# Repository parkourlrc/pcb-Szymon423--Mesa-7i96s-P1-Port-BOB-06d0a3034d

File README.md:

# Mesa 7i96S P1 I/O Breakout Board

This is a breakout board for the **P1 (DB25) expansion port of the [Mesa 7i96S](https://mesanet.com/)**. It turns the 17 raw 3.3 V GPIO pins of P1 into
**12 galvanically isolated 24 V inputs** and **5 solid-state relay outputs**. The outputs are on pluggable screw terminals, and the board sits on a 3D-printed DIN-rail mount.

| Front | Back |
| :---: | :--: |
|  |  |

---

## Features

- **12 inputs, 24 V, optically isolated.** Each input has a TLP293 optocoupler, a 74HC14 Schmitt-trigger buffer, a bidirectional TVS (SMF30CA), a ferrite-bead filter and a status LED.
- **5 outputs, solid-state relays.** The CPC1017N SSRs give isolated, polarity-free contacts that switch AC or DC. Each output has a status LED.
- **Pluggable 3.5 mm terminal blocks** (Phoenix MCV-style) on the field side.
- **26-pin IDC header** that connects to the 7i96S P1 with a standard IDC26 ⇄ DB25 ribbon cable.
- **Powered from the Mesa card.** The logic side takes +5 V from P1, behind a 100 mA fuse. The board needs no extra logic supply.
- **3D-printed DIN-rail mount.** STL, 3MF and Blender source are included.

## Specifications

| Parameter | Value |
| --- | --- |
| Inputs | 12, isolated, sourcing (PNP / +24 V = active) |
| Input voltage | 24 V nominal, clamped by 30 V TVS |
| Input current | ≈ 4–5 mA @ 24 V |
| Input isolation | Optocoupler; the input common (`GND` terminals) is separate from Mesa GND |
| Outputs | 5, SSR contacts (CPC1017N), AC/DC |
| Output voltage | max **30 V** |
| Output current | max **100 mA** per channel |
| Logic supply | +5 V from Mesa P1, fused 100 mA |
| PCB size | 52.5 × 98 mm, 2 layers |

## Pinout

### Field terminals (top → bottom, as printed on the silkscreen)

| Terminal | Signal | Mesa pin | LinuxCNC HAL pin |
| --- | --- | --- | --- |
| J5.1 | In12 | IO40 | `hm2_7i96s.0.gpio.040.in` |
| J5.2 | In11 | IO41 | `hm2_7i96s.0.gpio.041.in` |
| J5.3 | In10 | IO42 | `hm2_7i96s.0.gpio.042.in` |
| J5.4 | In9  | IO43 | `hm2_7i96s.0.gpio.043.in` |
| J5.5 | In8  | IO44 | `hm2_7i96s.0.gpio.044.in` |
| J5.6 | In7  | IO45 | `hm2_7i96s.0.gpio.045.in` |
| J3.1 | In6  | IO34 | `hm2_7i96s.0.gpio.034.in` |
| J3.2 | In5  | IO35 | `hm2_7i96s.0.gpio.035.in` |
| J3.3 | In4  | IO36 | `hm2_7i96s.0.gpio.036.in` |
| J3.4 | In3  | IO37 | `hm2_7i96s.0.gpio.037.in` |
| J3.5 | In2  | IO38 | `hm2_7i96s.0.gpio.038.in` |
| J3.6 | In1  | IO39 | `hm2_7i96s.0.gpio.039.in` |
| J4.1, J4.2 | GND (input common, isolated) | – | – |
| J4.3 / J4.4 | Out5 A / B | IO46 | `hm2_7i96s.0.gpio.046.out` |
| J4.5 / J4.6 | Out4 A / B | IO47 | `hm2_7i96s.0.gpio.047.out` |
| J6.1 / J6.2 | Out3 A / B | IO48 | `hm2_7i96s.0.gpio.048.out` |
| J6.3 / J6.4 | Out2 A / B | IO49 | `hm2_7i96s.0.gpio.049.out` |
| J6.5 / J6.6 | Out1 A / B | IO50 | `hm2_7i96s.0.gpio.050.out` |

### Mesa connector (J7, IDC 2×13)

| J7 pin | DB25 pin* | Signal |
| --- | --- | --- |
| 1, 2, 3, 4, 5, 6, 7, 8, 9 | 1, 14, 2, 15, 3, 16, 4, 17, 5 | IO34 … IO42 |
| 11, 13, 15 | 6, 7, 8 | IO43, IO44, IO45 |
| 17, 19, 21, 23, 25 | 9, 10, 11, 12, 13 | IO46 … IO50 |
| 10, 12, 14, 16 | 18, 19, 20, 21 | GND |
| 18, 20, 22, 24 | 22, 23, 24, 25 | +5 V (from Mesa) |
| 26 | – | not connected |

\* With a standard flat IDC26 ⇄ DB25 cable.

> [!IMPORTANT]
> The board takes its logic power from the +5 V on the P1 connector. Check in the 7i96S manual that +5 V is enabled on P1.

## Wiring

**Inputs.** Each input is active when +24 V is applied to the `InX` terminal relative to the `GND` terminals (J4.1/J4.2). Connect the 0 V of your 24 V field supply to `GND`. This suits PNP (sourcing) sensors, switches to +24 V, and similar. The input common is **not** connected to Mesa ground, so isolation is preserved.

```
+24V ──[switch / PNP sensor]──► InX
0V   ─────────────────────────► GND (J4.1 / J4.2)
```

**Outputs.** Each output is a floating SSR contact between `OutXA` and `OutXB`. Wire it like a relay contact in series with the load. It works for DC or AC up to 30 V and 100 mA, which is enough for a relay coil, a pilot light or a PLC input. Use an external relay or contactor for bigger loads, and use a flyback diode on inductive DC loads.

```
+V ──[load]──► OutXA   OutXB ──► 0V
```

## LinuxCNC configuration

The P1 pins must be configured as plain GPIO in the 7i96S firmware. Input polarity is not inverted: an active input reads `TRUE`. An output set to `TRUE` closes the SSR.

```hal
# Outputs: P1 GPIO are inputs by default
setp hm2_7i96s.0.gpio.046.is_output true
setp hm2_7i96s.0.gpio.047.is_output true
setp hm2_7i96s.0.gpio.048.is_output true
setp hm2_7i96s.0.gpio.049.is_output true
setp hm2_7i96s.0.gpio.050.is_output true

# Examples
net spindle-cw     spindle.0.forward          => hm2_7i96s.0.gpio.050.out   # Out1
net coolant-flood  iocontrol.0.coolant-flood  => hm2_7i96s.0.gpio.049.out   # Out2

net probe-in       hm2_7i96s.0.gpio.039.in    => motion.probe-input         # In1
net tool-setter    hm2_7i96s.0.gpio.038.in    => motion.digital-in-00       # In2
```

## License

This project is licensed under [**Creative Commons Attribution 4.0 International (CC BY 4.0)**](LICENSE).

You may use, modify, manufacture and sell the design, including commercially, provided that you **credit the author**. For example:

> Based on *Mesa 7i96S P1 I/O Breakout Board* by Szymon Wąchała – https://github.com/Szymon423/24-DB25-BOB-IO

Author: **Szymon Wąchała**

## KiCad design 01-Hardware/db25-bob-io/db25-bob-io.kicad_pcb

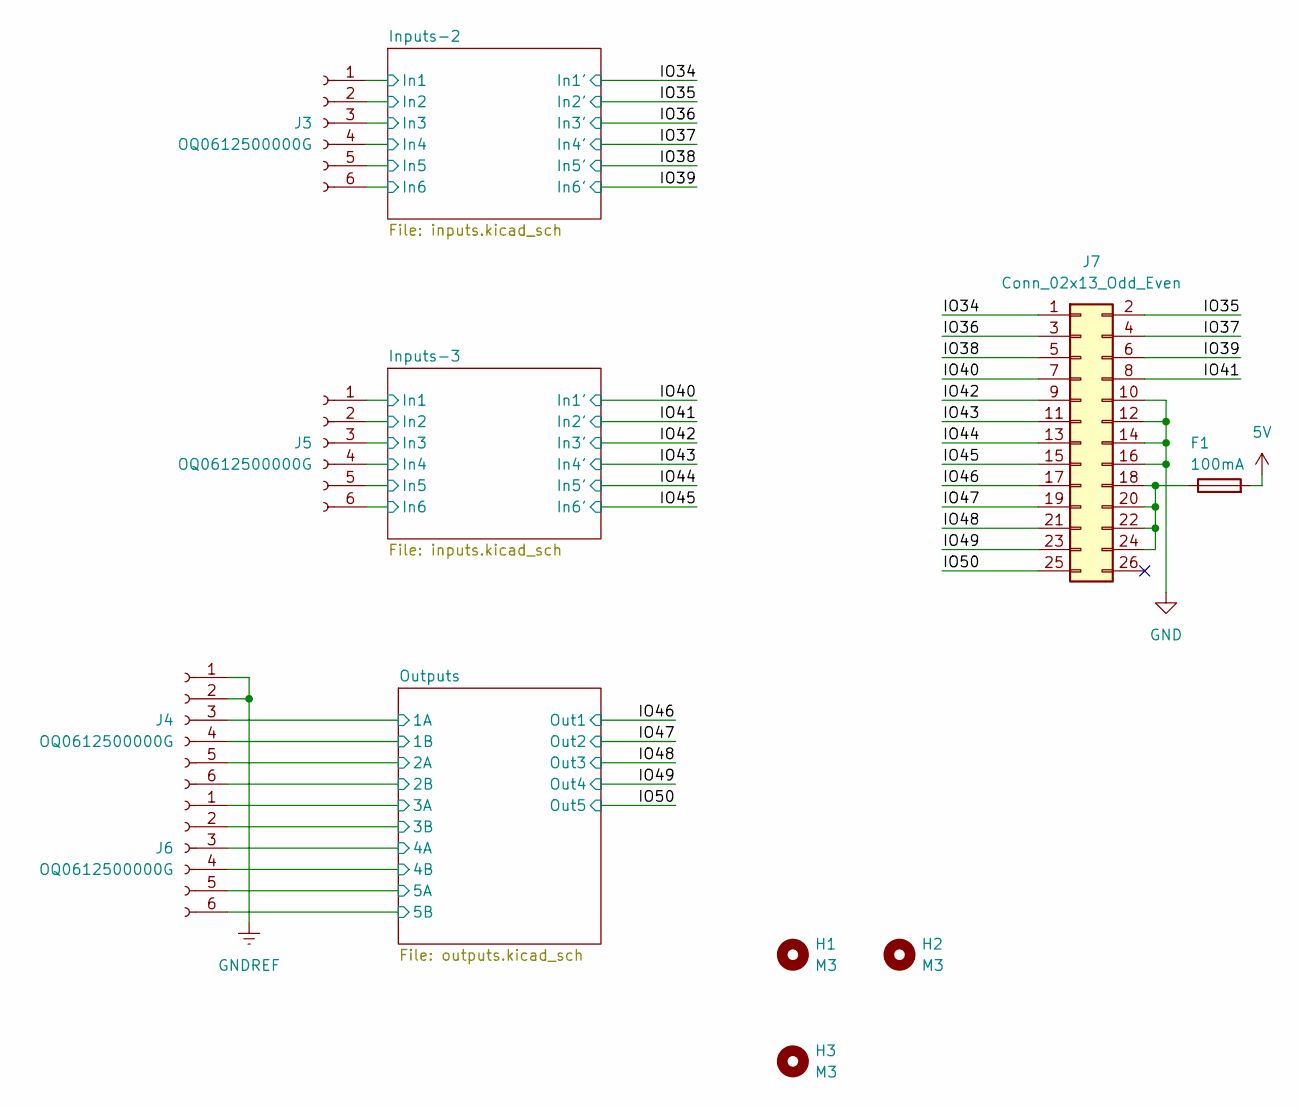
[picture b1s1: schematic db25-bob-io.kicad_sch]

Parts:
F1: 100mA; Fuse_1206_3216Metric
H1, H2, H3: M3; MountingHole_3.2mm_M3
J3, J4, J5, J6: OQ0612500000G; PhoenixContact_MCV_1,5_6-G-3.5_1x06_P3.50mm_Vertical
J7: Conn_02x13_Odd_Even; IDC-Header_2x13_P2.54mm_Vertical

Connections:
5V: F1.2; also elsewhere on the board
/IO34: J7.1; also elsewhere on the board
/IO35: J7.2; also elsewhere on the board
/IO36: J7.3; also elsewhere on the board
/IO37: J7.4; also elsewhere on the board
/IO38: J7.5; also elsewhere on the board
/IO39: J7.6; also elsewhere on the board
/IO40: J7.7; also elsewhere on the board
/IO41: J7.8; also elsewhere on the board
/IO42: J7.9; also elsewhere on the board
/IO43: J7.11; also elsewhere on the board
/IO44: J7.13; also elsewhere on the board
/IO45: J7.15; also elsewhere on the board
/IO46: J7.17; also elsewhere on the board
/IO47: J7.19; also elsewhere on the board
/IO48: J7.21; also elsewhere on the board
/IO49: J7.23; also elsewhere on the board
/IO50: J7.25; also elsewhere on the board
/Inputs-2/In1: J3.1; also elsewhere on the board
/Inputs-2/In2: J3.2; also elsewhere on the board
/Inputs-2/In3: J3.3; also elsewhere on the board
/Inputs-2/In4: J3.4; also elsewhere on the board
/Inputs-2/In5: J3.5; also elsewhere on the board
/Inputs-2/In6: J3.6; also elsewhere on the board
/Inputs-3/In1: J5.1; also elsewhere on the board
/Inputs-3/In2: J5.2; also elsewhere on the board
/Inputs-3/In3: J5.3; also elsewhere on the board
/Inputs-3/In4: J5.4; also elsewhere on the board
/Inputs-3/In5: J5.5; also elsewhere on the board
/Inputs-3/In6: J5.6; also elsewhere on the board
/Outputs/1A: J4.3; also elsewhere on the board
/Outputs/1B: J4.4; also elsewhere on the board
/Outputs/2A: J4.5; also elsewhere on the board
/Outputs/2B: J4.6; also elsewhere on the board
/Outputs/3A: J6.1; also elsewhere on the board
/Outputs/3B: J6.2; also elsewhere on the board
/Outputs/4A: J6.3; also elsewhere on the board
/Outputs/4B: J6.4; also elsewhere on the board
/Outputs/5A: J6.5; also elsewhere on the board
/Outputs/5B: J6.6; also elsewhere on the board
GND: J7.10, J7.12, J7.14, J7.16; also elsewhere on the board
GNDREF: J4.1, J4.2; also elsewhere on the board
unnamed: F1.1, J7.18, J7.20, J7.22, J7.24

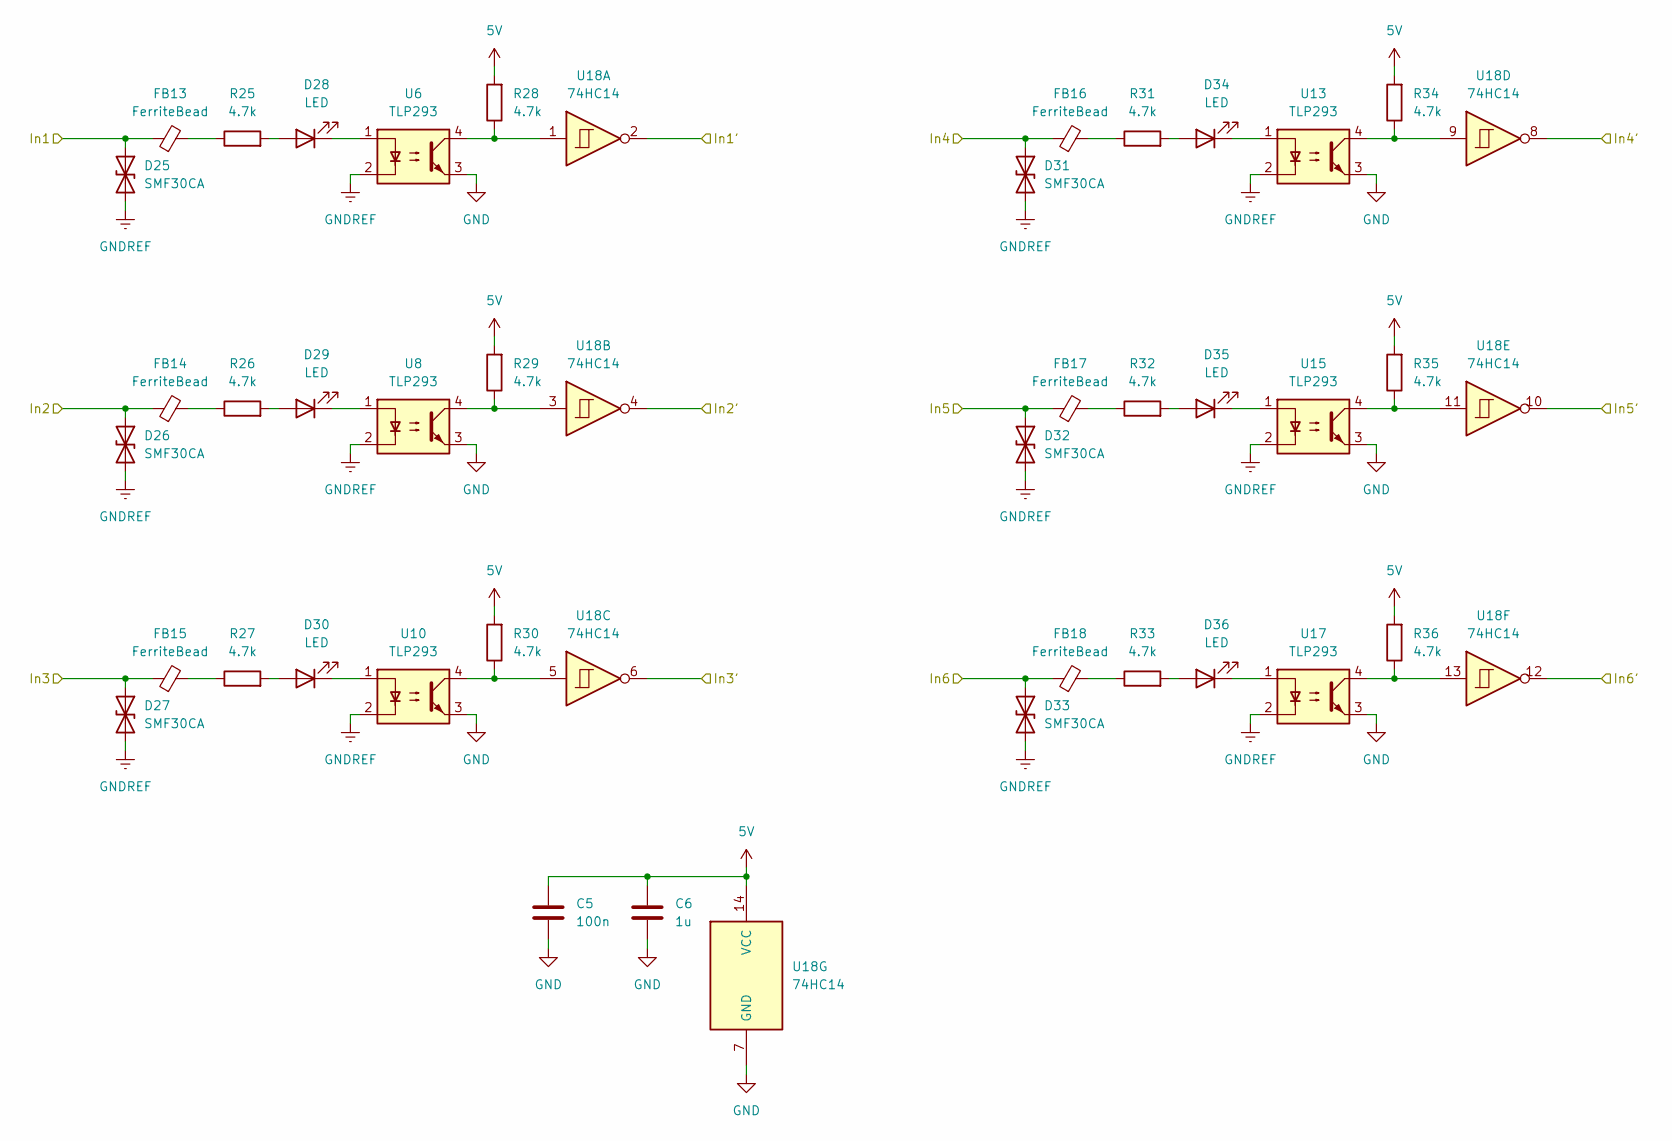
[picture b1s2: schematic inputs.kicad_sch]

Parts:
C5: 100n; C_0603_1608Metric
C6: 1u; C_0603_1608Metric
D25, D26, D27, D31, D32, D33: SMF30CA; D_SOD-123F
D28, D29, D30, D34, D35, D36: LED; LED_0603_1608Metric
FB13, FB14, FB15, FB16, FB17, FB18: FerriteBead; L_0603_1608Metric
R25, R26, R27, R28, R29, R30, R31, R32, R33, R34, R35, R36: 4.7k; R_0805_2012Metric
U6, U8, U10, U13, U15, U17: TLP293; SOIC-4_4.55x2.6mm_P1.27mm
U18: 74HC14; SO-14_3.9x8.65mm_P1.27mm

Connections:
5V: C5.1, C6.1, R28.2, R29.2, R30.2, R34.2, R35.2, R36.2, U18.14 (VCC); also elsewhere on the board
/IO40: U18.2; also elsewhere on the board
/IO41: U18.4; also elsewhere on the board
/IO42: U18.6; also elsewhere on the board
/IO43: U18.8; also elsewhere on the board
/IO44: U18.10; also elsewhere on the board
/IO45: U18.12; also elsewhere on the board
/Inputs-3/In1: D25.1 (A1), FB13.1; also elsewhere on the board
/Inputs-3/In2: D26.1 (A1), FB14.1; also elsewhere on the board
/Inputs-3/In3: D27.1 (A1), FB15.1; also elsewhere on the board
/Inputs-3/In4: D31.1 (A1), FB16.1; also elsewhere on the board
/Inputs-3/In5: D32.1 (A1), FB17.1; also elsewhere on the board
/Inputs-3/In6: D33.1 (A1), FB18.1; also elsewhere on the board
GND: C5.2, C6.2, U6.3, U8.3, U10.3, U13.3, U15.3, U17.3, U18.7 (GND); also elsewhere on the board
GNDREF: D25.2 (A2), D26.2 (A2), D27.2 (A2), D31.2 (A2), D32.2 (A2), D33.2 (A2), U6.2, U8.2, U10.2, U13.2, U15.2, U17.2; also elsewhere on the board
unnamed: D28.2 (A), R25.2
unnamed: D28.1 (K), U6.1
unnamed: D29.2 (A), R26.2
unnamed: D29.1 (K), U8.1
unnamed: D30.2 (A), R27.2
unnamed: D30.1 (K), U10.1
unnamed: D34.2 (A), R31.2
unnamed: D34.1 (K), U13.1
unnamed: D35.2 (A), R32.2
unnamed: D35.1 (K), U15.1
unnamed: D36.2 (A), R33.2
unnamed: D36.1 (K), U17.1
unnamed: FB13.2, R25.1
unnamed: FB14.2, R26.1
unnamed: FB15.2, R27.1
unnamed: FB16.2, R31.1
unnamed: FB17.2, R32.1
unnamed: FB18.2, R33.1
unnamed: R28.1, U6.4, U18.1
unnamed: R29.1, U8.4, U18.3
unnamed: R30.1, U10.4, U18.5
unnamed: R34.1, U13.4, U18.9
unnamed: R35.1, U15.4, U18.11
unnamed: R36.1, U17.4, U18.13

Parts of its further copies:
C3: 100n; C_0603_1608Metric
C4: 1u; C_0603_1608Metric
D13, D14, D15, D19, D20, D21: SMF30CA; D_SOD-123F
D16, D17, D18, D22, D23, D24: LED; LED_0603_1608Metric
FB7, FB8, FB9, FB10, FB11, FB12: FerriteBead; L_0603_1608Metric
R13, R14, R15, R16, R17, R18, R19, R20, R21, R22, R23, R24: 4.7k; R_0805_2012Metric
U7, U9, U12, U14, U16, U19: TLP293; SOIC-4_4.55x2.6mm_P1.27mm
U11: 74HC14; SO-14_3.9x8.65mm_P1.27mm

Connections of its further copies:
5V: C3.1, C4.1, R16.2, R17.2, R18.2, R22.2, R23.2, R24.2, U11.14 (VCC); also elsewhere on the board
/IO34: U11.2; also elsewhere on the board
/IO35: U11.4; also elsewhere on the board
/IO36: U11.6; also elsewhere on the board
/IO37: U11.8; also elsewhere on the board
/IO38: U11.10; also elsewhere on the board
/IO39: U11.12; also elsewhere on the board
/Inputs-2/In1: D13.1 (A1), FB7.1; also elsewhere on the board
/Inputs-2/In2: D14.1 (A1), FB8.1; also elsewhere on the board
/Inputs-2/In3: D15.1 (A1), FB9.1; also elsewhere on the board
/Inputs-2/In4: D19.1 (A1), FB10.1; also elsewhere on the board
/Inputs-2/In5: D20.1 (A1), FB11.1; also elsewhere on the board
/Inputs-2/In6: D21.1 (A1), FB12.1; also elsewhere on the board
GND: C3.2, C4.2, U7.3, U9.3, U11.7 (GND), U12.3, U14.3, U16.3, U19.3; also elsewhere on the board
GNDREF: D13.2 (A2), D14.2 (A2), D15.2 (A2), D19.2 (A2), D20.2 (A2), D21.2 (A2), U7.2, U9.2, U12.2, U14.2, U16.2, U19.2; also elsewhere on the board
unnamed: D16.2 (A), R13.2
unnamed: D16.1 (K), U7.1
unnamed: D17.2 (A), R14.2
unnamed: D17.1 (K), U9.1
unnamed: D18.2 (A), R15.2
unnamed: D18.1 (K), U12.1
unnamed: D22.2 (A), R19.2
unnamed: D22.1 (K), U14.1
unnamed: D23.2 (A), R20.2
unnamed: D23.1 (K), U16.1
unnamed: D24.2 (A), R21.2
unnamed: D24.1 (K), U19.1
unnamed: FB7.2, R13.1
unnamed: FB8.2, R14.1
unnamed: FB9.2, R15.1
unnamed: FB10.2, R19.1
unnamed: FB11.2, R20.1
unnamed: FB12.2, R21.1
unnamed: R16.1, U7.4, U11.1
unnamed: R17.1, U9.4, U11.3
unnamed: R18.1, U11.5, U12.4
unnamed: R22.1, U11.9, U14.4
unnamed: R23.1, U11.11, U16.4
unnamed: R24.1, U11.13, U19.4

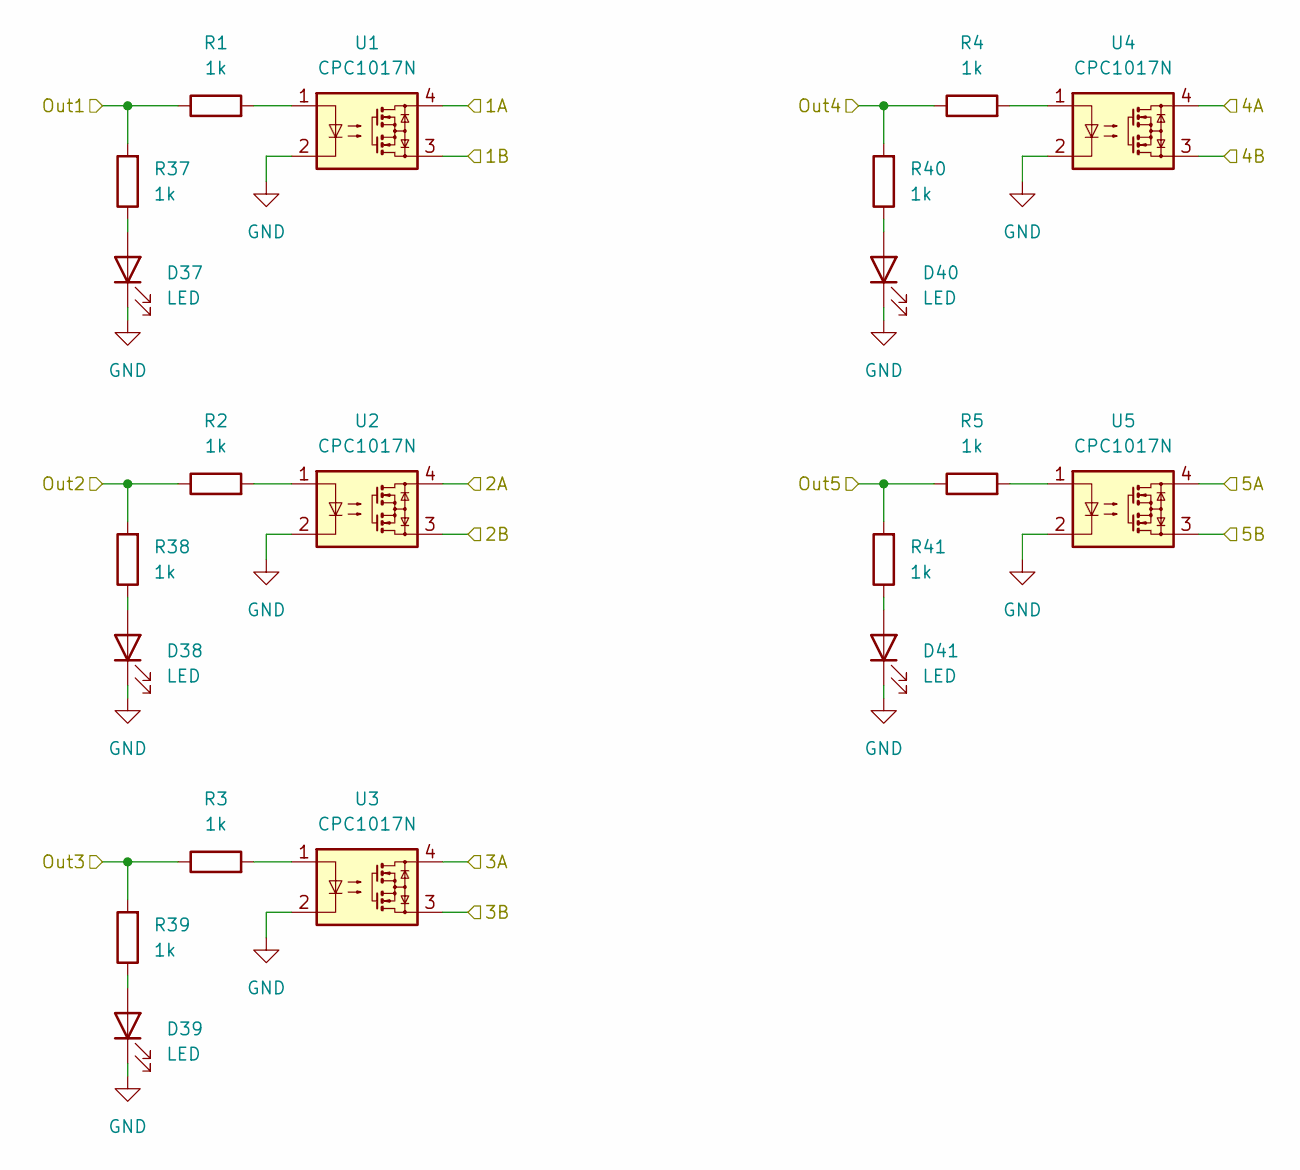
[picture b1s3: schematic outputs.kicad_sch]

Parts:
D37, D38, D39, D40, D41: LED; LED_0603_1608Metric
R1, R2, R3, R4, R5, R37, R38, R39, R40, R41: 1k; R_0603_1608Metric
U1, U2, U3, U4, U5: CPC1017N; SOP-4_3.8x4.1mm_P2.54mm

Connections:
/IO46: R1.1, R37.2; also elsewhere on the board
/IO47: R2.1, R38.2; also elsewhere on the board
/IO48: R3.1, R39.2; also elsewhere on the board
/IO49: R4.1, R40.2; also elsewhere on the board
/IO50: R5.1, R41.2; also elsewhere on the board
/Outputs/1A: U1.4; also elsewhere on the board
/Outputs/1B: U1.3; also elsewhere on the board
/Outputs/2A: U2.4; also elsewhere on the board
/Outputs/2B: U2.3; also elsewhere on the board
/Outputs/3A: U3.4; also elsewhere on the board
/Outputs/3B: U3.3; also elsewhere on the board
/Outputs/4A: U4.4; also elsewhere on the board
/Outputs/4B: U4.3; also elsewhere on the board
/Outputs/5A: U5.4; also elsewhere on the board
/Outputs/5B: U5.3; also elsewhere on the board
GND: D37.1 (K), D38.1 (K), D39.1 (K), D40.1 (K), D41.1 (K), U1.2, U2.2, U3.2, U4.2, U5.2; also elsewhere on the board
unnamed: D37.2 (A), R37.1
unnamed: D38.2 (A), R38.1
unnamed: D39.2 (A), R39.1
unnamed: D40.2 (A), R40.1
unnamed: D41.2 (A), R41.1
unnamed: R1.2, U1.1
unnamed: R2.2, U2.1
unnamed: R3.2, U3.1
unnamed: R4.2, U4.1
unnamed: R5.2, U5.1

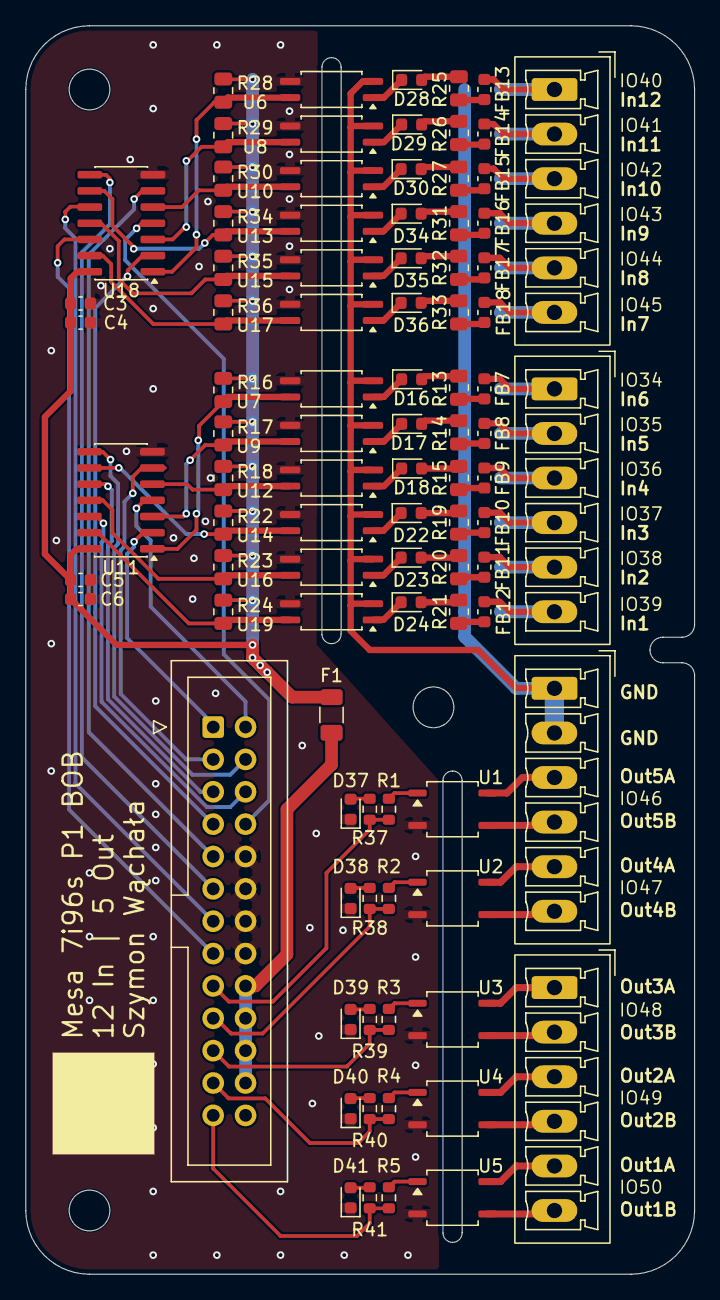
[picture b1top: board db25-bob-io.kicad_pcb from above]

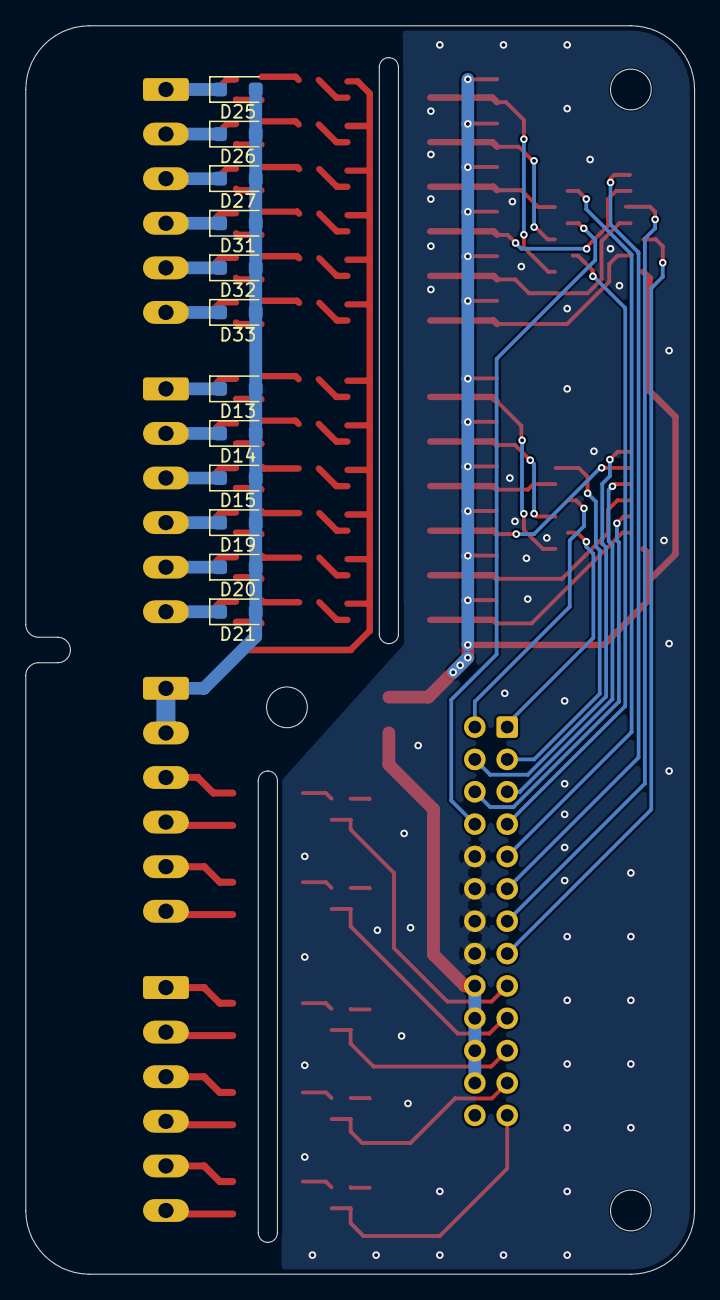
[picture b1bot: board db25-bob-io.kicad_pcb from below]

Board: 2 copper layers, 52.5 x 98.0 mm, 107 parts (12 on the bottom side), 101 nets.

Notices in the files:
README.md:
License: CC BY 4.0
